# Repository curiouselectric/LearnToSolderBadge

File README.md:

LearnToSolderBadge
==================

KiCAD files for a couple of simple Learn-to-solder flashing LED badges. Done for Nottingham Hackspace.
The KiCAD projects are available and also the gerber files for PCB production.

There are two versions of the learn to solder badge:

Circle Badge - a simple circular PCB.
Robot Badge - a robot shaped PCB with surface mount options.

There are also notes and datasheets on the parts required and where to get them from.

These were designed by Matt Little (matt@re-innovation.co.uk) for doing soldering workshops at Nottingham Hackspace.

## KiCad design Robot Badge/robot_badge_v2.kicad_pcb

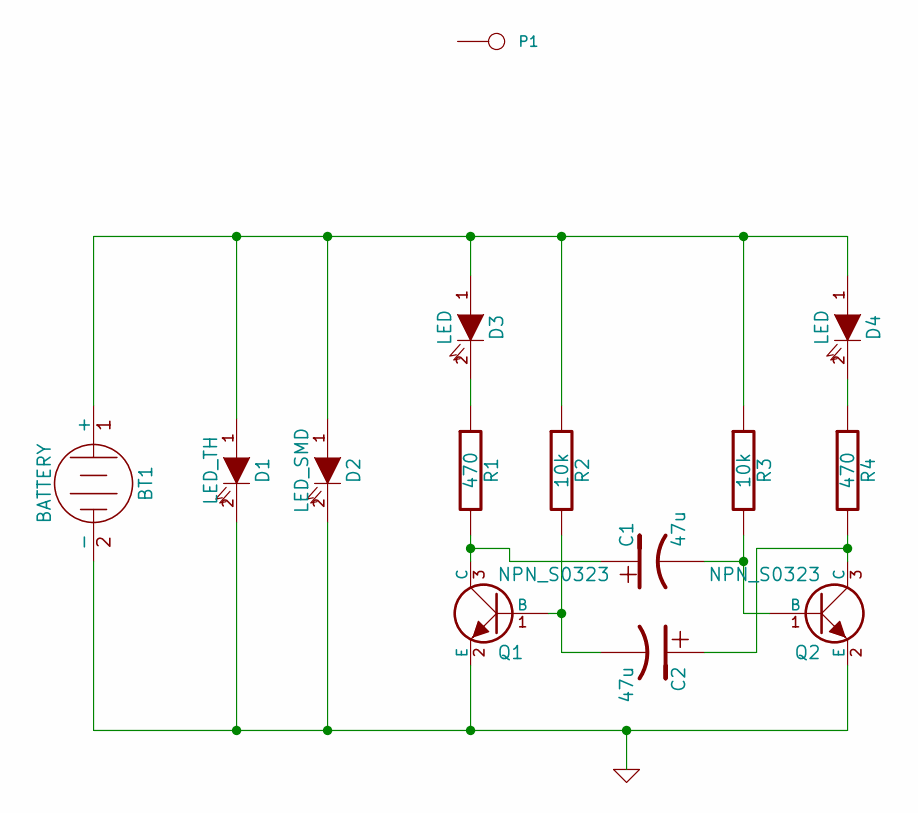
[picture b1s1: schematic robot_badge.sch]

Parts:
BT1: BATTERY
C1, C2: 47u
D1: LED_TH
D2: LED_SMD
D3, D4: LED
P1: CONN_1
Q1, Q2: NPN_S0323
R1, R4: 470
R2, R3: 10k

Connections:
GND: BT1.2 (-), D1.2 (K), D2.2 (K), Q1.2 (E), Q2.2 (E)
unnamed: C1.1, Q1.3 (C), R1.2
unnamed: C2.2, Q1.1 (B), R2.2
unnamed: C2.1, Q2.3 (C), R4.2
unnamed: D3.2 (K), R1.1
unnamed: BT1.1 (+), D1.1 (A), D2.1 (A), D3.1 (A), D4.1 (A), R2.1, R3.1
unnamed: D4.2 (K), R4.1
unnamed: C1.2, Q2.1 (B), R3.2

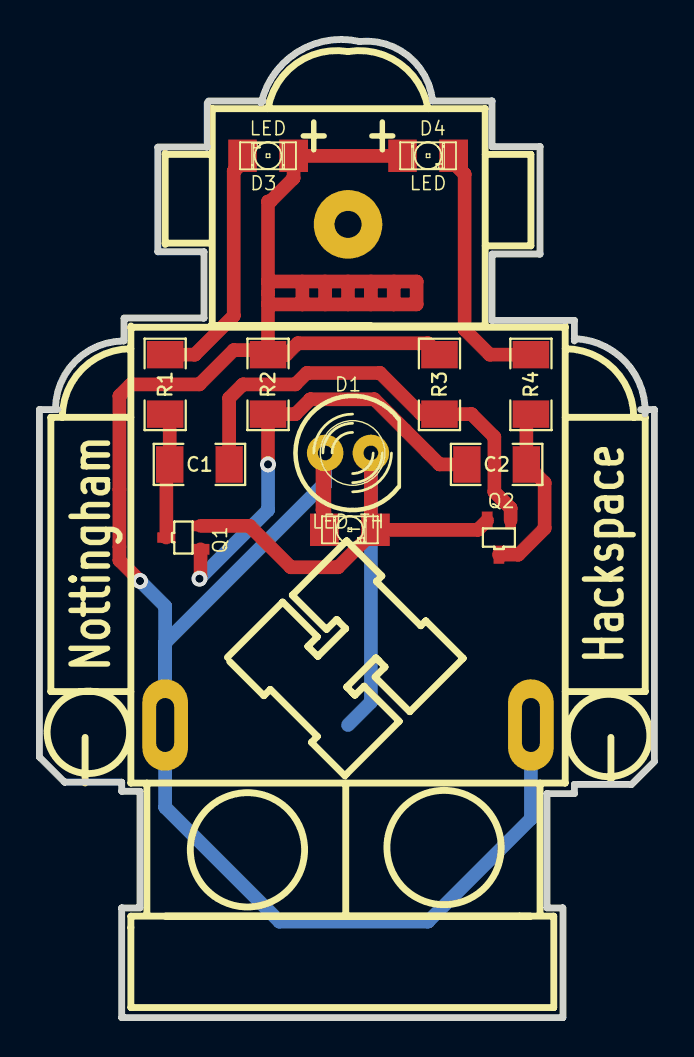
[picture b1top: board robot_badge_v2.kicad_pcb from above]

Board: 2 copper layers, 34.2 x 54.3 mm, 15 parts (0 on the bottom side), 8 nets.

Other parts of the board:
RB1: ROBOT; robot

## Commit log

2014-08-23 Upload main code
    Uploaded both types of badge Kicad files
